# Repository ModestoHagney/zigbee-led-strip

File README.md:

| Supported Targets | ESP32-C6 | ESP32-H2 |
| ----------------- | -------- | -------- |

# Zigbee LED Strip

Firmware that turns an ESP32-H2 or ESP32-C6 and a WS2812 strip into a
Zigbee colour light. It joins the network as a router (it relays for
other Zigbee devices, like a mains-powered bulb) and shows up in Home
Assistant as one colour dimmable light (on/off, brightness, and colour
in either hue/saturation or XY).

The whole strip is one light: every pixel gets the same colour.

## Boards

One source builds for both chips. `main/config.h` picks the settings
from the chip target:

| Target   | LED data pin | LED count | Zigbee model |
|----------|--------------|-----------|--------------|
| ESP32-H2 | GPIO 22      | 64        | `H2-LED`     |
| ESP32-C6 | GPIO 19      | 144       | `C6-LED`     |

The LED count in the table is only the default, see Settings below.
Manufacturer name is `NiftyFish`. Power source and the Zigbee endpoint
are set in `main/config.h`.

## Settings in Home Assistant

These are changed on the device page in Home Assistant (ZHA) and saved
on the board. `main/config.h` holds the defaults a freshly flashed board
starts with.

| Setting | Range | Notes |
|---------|-------|-------|
| LED count | 1 to 1024 | |
| Colour order | GRB, RGB, BRG, RBG, GBR, BGR | for strips that show the wrong colours |
| LED type | RGB, RGBW | RGBW sends white to the strip's white LED |
| Max current | 0 to 65000 mA | dims the strip to stay under it, 0 = no limit |
| White balance red, green, blue | 0 to 100 % | so white matches other bulbs |
| Dimming curve | 10 to 30 | 10 = straight, 22 = like most bulbs |
| Zigbee transmit power | -24 to 20 dBm | |
| Start-up behaviour | off, on, toggle, previous | what the strip does when power returns |
| On/off transition time | tenths of a second | fade when switching, 0 = no fade |

The last two are standard Zigbee settings that ZHA shows by itself. The
rest need the quirk file: copy `homeassistant/niftyfish_led.py` to
`/config/zha_quirks/` in Home Assistant, add this to
`configuration.yaml` and restart:

```yaml
zha:
  custom_quirks_path: /config/zha_quirks/
```

The device also reports the chip temperature and an estimated strip
power. The estimate is worked out from colour, brightness and LED count
with `LED_MA_PER_CHANNEL` and `LED_VOLTS` from `main/config.h`; the
current limit uses the same numbers.

The Identify button blinks the strip white.

The last colour, brightness and on/off state are saved a few seconds
after they change and come back after a power cut.

## Hardware

`hardware/ZigbeeLEDController/` is the KiCad 9 project for the
controller board: an ESP32-C6-MINI-1 with a USB-C input, a CH221K USB
PD sink, an AP63203 3.3 V buck regulator and an LED strip output. The
folder also has the PCBWay fabrication zip (`.kicad_pcb.zip`: gerbers,
BOM and positions) and a STEP export of the board.

## Build and flash

Needs ESP-IDF 5.x (built with v5.5.2).

```
idf.py set-target esp32h2
idf.py -p PORT flash monitor
```

Use `esp32c6` for the C6 board. Switching target regenerates
`sdkconfig` and `dependencies.lock`; neither is committed.

Run `idf.py -p PORT erase-flash` first if the board has been paired
before and you want it to join as a new device. This is also needed
once for a board flashed before wireless updates were added, because
the partition layout changed; then remove it from ZHA and pair it again.

An existing `sdkconfig` keeps the old end-device setting. Delete it (or
run `idf.py set-target` again) so `sdkconfig.defaults` applies.

The partition table has two firmware slots of 896 KB each and fits 2 MB
flash.

## Wireless updates

After the first USB flash, new firmware can be sent over Zigbee from
Home Assistant. Home Assistant downloads it from the `firmware` branch
of this repo, so the repo has to be public.

One-time setup in Home Assistant: add this to `configuration.yaml` and
restart.

```yaml
zha:
  zigpy_config:
    ota:
      extra_providers:
        - type: z2m
          url: https://raw.githubusercontent.com/ModestoHagney/zigbee-led-strip/firmware/index.json
```

Home Assistant checks that index once a day (and when it restarts). A
board asks Home Assistant for updates when it joins and then every
hour; when a newer version is listed, its Firmware entity offers it.

To publish an update:

1. Raise `FW_VERSION` in `main/config.h`.
2. `idf.py build`, once per chip.
3. `python tools/make_ota.py` writes `build/niftyfish-<chip>-led-v<version>.ota`.
4. On the `firmware` branch, replace the old `.ota` file with the new
   one, then run
   `python tools/make_index.py . https://raw.githubusercontent.com/ModestoHagney/zigbee-led-strip/firmware`
   and commit and push.

The `firmware` branch also carries the 4-button light's update file, so
one line in Home Assistant covers every NiftyFish device.

An H2 file is never offered to a C6 board, or a strip file to the
4-button light: each has its own image type. If new firmware crashes
before it starts Zigbee, the board goes back to the previous one on the
next boot.

Without GitHub: put the `.ota` file in a folder on the Home Assistant
machine and list that folder as a `type: advanced` provider instead
(ZHA's documentation has the exact lines).

## Pairing

On first boot (or after an erase) the device starts network steering
on its own. Put the coordinator into permit-join and it should log
`joined network! ready.`

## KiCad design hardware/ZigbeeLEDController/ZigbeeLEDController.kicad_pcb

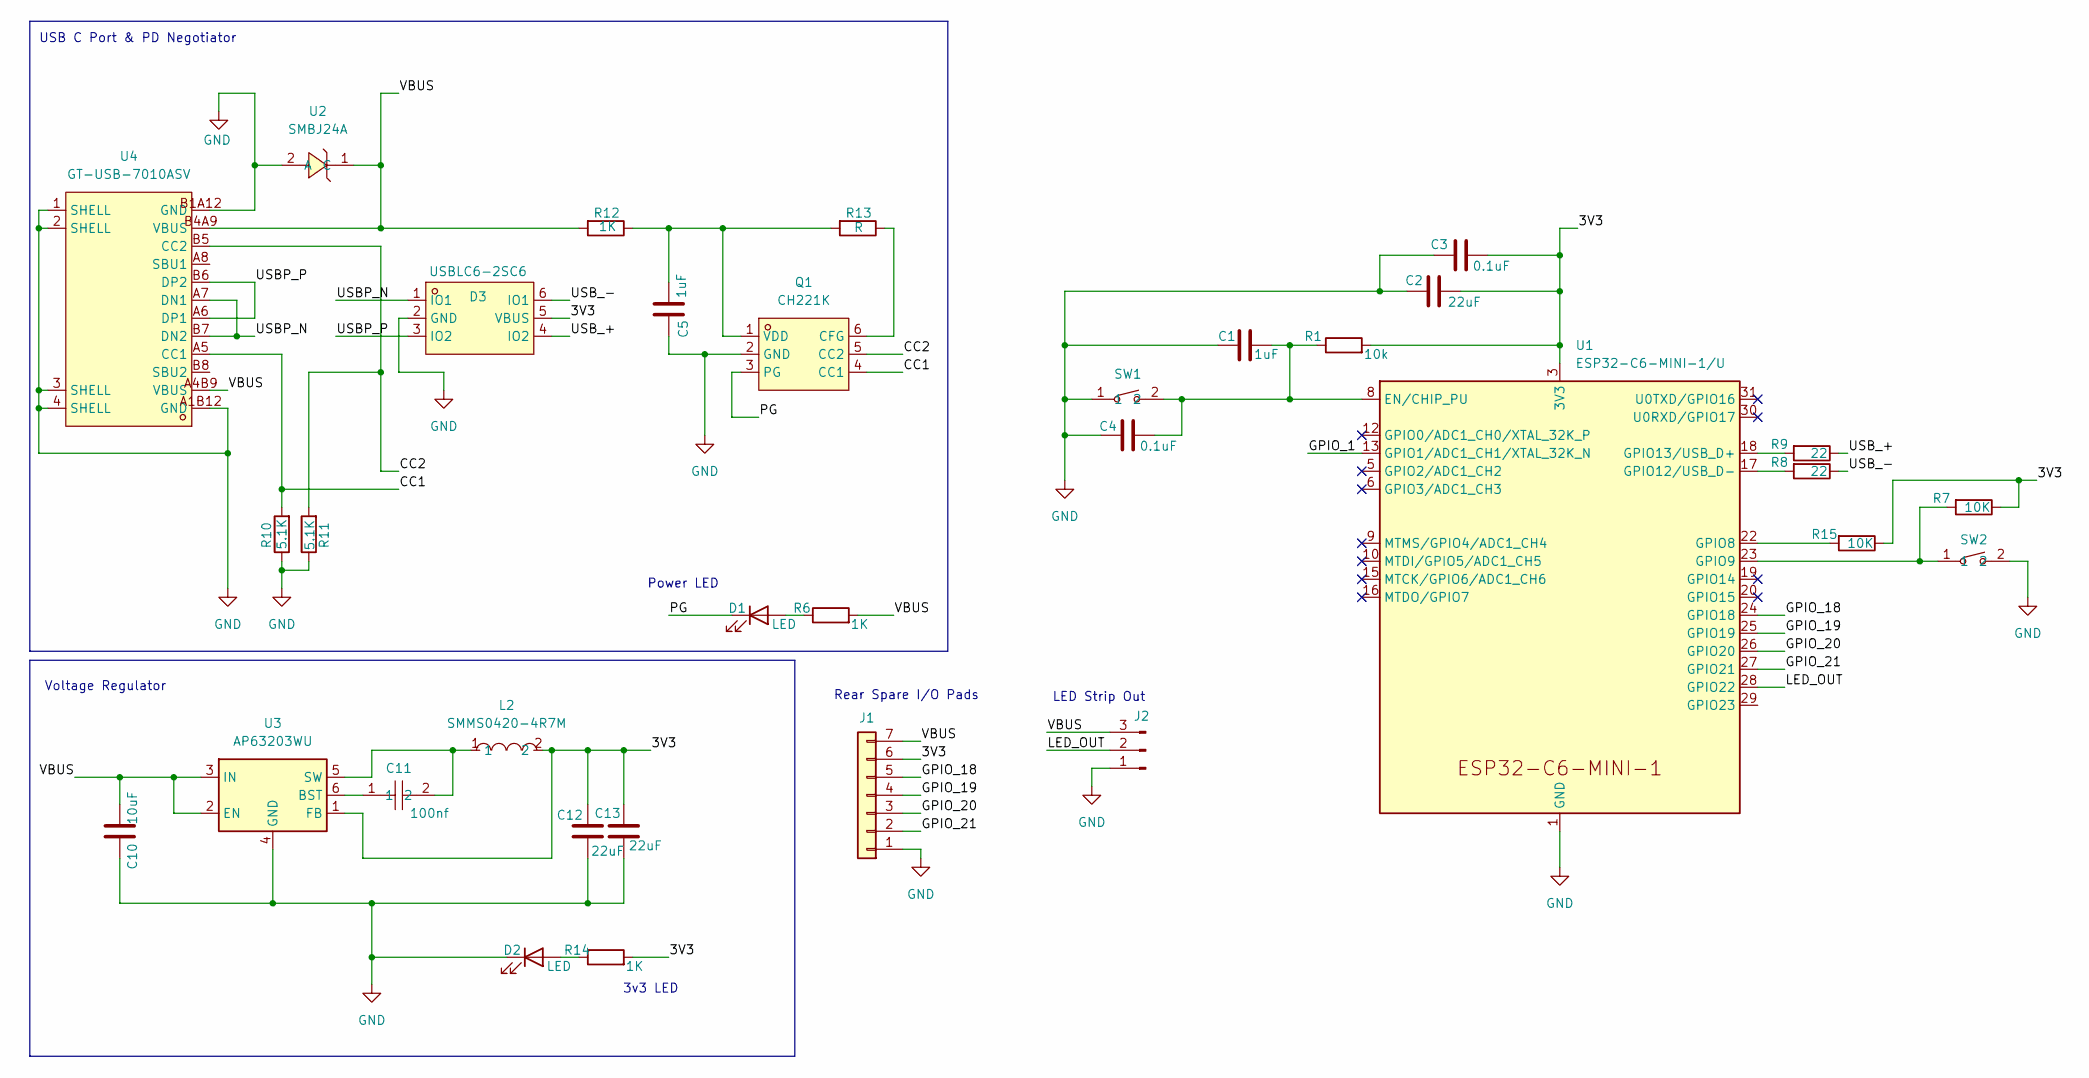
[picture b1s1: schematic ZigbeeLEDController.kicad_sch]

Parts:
C1, C5: 1uF; C_0805_2012Metric
C2, C12, C13: 22uF; C_0805_2012Metric
C3, C4: 0.1uF; C_0805_2012Metric
C10: 10uF; C_0805_2012Metric
C11: 100nf; C_0805_2012Metric; MPN CC0805KRX7R9BB104; LCSC Part C49678
D1, D2: LED; LED_0805_2012Metric
D3: USBLC6-2SC6; SOT-23-6_L2.9-W1.6-P0.95-LS2.8-BL; MPN USBLC6-2SC6; LCSC Part C2827654
J1: Conn_01x07; 1x07_SOLDER_PAD_1.7x4_LABEL
J2: Conn_01x03_Pin; PinSocket_1x03_P2.54mm_Vertical
L2: SMMS0420-4R7M; IND-SMD_L4.8-W4.5; MPN SMMS0420-4R7M; LCSC Part C133193
Q1: CH221K; SOT-23-6_L2.9-W1.6-P0.95-LS2.8-BL-2; MPN CH221K; LCSC Part C5125736
R1: 10k; R_0805_2012Metric
R6, R12, R14: 1K; R_0805_2012Metric
R7, R15: 10K; R_0805_2012Metric
R8, R9: 22; R_0805_2012Metric
R10, R11: 5.1K; R_0805_2012Metric
R13: R; R_0805_2012Metric
SW1, SW2: HX-B3U-1000P-1.6N; SW-SMD_2P-L3.0-W2.5-LS4.0; MPN HX-B3U-1000P-1.6N; LCSC Part C49234121
U1: ESP32-C6-MINI-1/U; ESP32-C6-MINI-1
U2: SMBJ24A; SMB_L4.3-W3.6-LS5.3-RD; MPN SMBJ24A; LCSC Part C19077578
U3: AP63203WU; TSOT-23-6
U4: GT-USB-7010ASV; USB-C-SMD_G-SWITCH_GT-USB-7010ASV; MPN GT-USB-7010ASV; LCSC Part C2988369

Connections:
/3V3: C2.2, C3.2, C12.1, C13.1, D3.5 (VBUS), J1.6, L2.2, R1.2, R7.1, R14.2, R15.1, U1.3 (3V3), U3.1 (FB)
/CC1: Q1.4 (CC1), R10.2, U4.A5 (CC1)
/CC2: Q1.5 (CC2), R11.2, U4.B5 (CC2)
/GPIO_1: U1.13 (GPIO1/ADC1_CH1/XTAL_32K_N)
/GPIO_18: J1.5, U1.24 (GPIO18)
/GPIO_19: J1.4, U1.25 (GPIO19)
/GPIO_20: J1.3, U1.26 (GPIO20)
/GPIO_21: J1.2, U1.27 (GPIO21)
/LED_OUT: J2.2, U1.28 (GPIO22)
/PG: D1.1 (K), Q1.3 (PG)
/USBP_N: D3.1 (IO1), U4.A7 (DN1), U4.B7 (DN2)
/USBP_P: D3.3 (IO2), U4.A6 (DP1), U4.B6 (DP2)
/USB_+: D3.4 (IO2), R9.1
/USB_-: D3.6 (IO1), R8.1
/VBUS: C10.1, J1.7, J2.3, R6.2, R12.2, U2.1 (C), U3.2 (EN), U3.3 (IN), U4.A4B9 (VBUS), U4.B4A9 (VBUS)
GND: C1.1, C2.1, C3.1, C4.2, C5.2, C10.2, C12.2, C13.2, D2.1 (K), D3.2 (GND), J1.1, J2.1, Q1.2 (GND), R10.1, R11.1, SW1.1, SW2.2, U1.1 (GND), U1.2 (GND), U1.11 (GND), U1.14 (GND), U1.36 (GND), U1.37 (GND), U1.38 (GND), U1.39 (GND), U1.40 (GND), U1.41 (GND), U1.42 (GND), U1.43 (GND), U1.44 (GND), U1.45 (GND), U1.46 (GND), U1.47 (GND), U1.48 (GND), U1.49 (GND), U1.50 (GND), U1.51 (GND), U1.52 (GND), U1.53 (GND), U2.2 (A), U3.4 (GND), U4.1 (SHELL), U4.2 (SHELL), U4.3 (SHELL), U4.4 (SHELL), U4.A1B12 (GND), U4.B1A12 (GND)
unnamed: D1.2 (A), R6.1
unnamed: D2.2 (A), R14.1
unnamed: Q1.6 (CFG), R13.1
unnamed: C5.1, Q1.1 (VDD), R12.1, R13.2
unnamed: C1.2, C4.1, R1.1, SW1.2, U1.8 (EN/CHIP_PU)
unnamed: R15.2, U1.22 (GPIO8)
unnamed: R7.2, SW2.1, U1.23 (GPIO9)
unnamed: R8.2, U1.17 (GPIO12/USB_D-)
unnamed: R9.2, U1.18 (GPIO13/USB_D+)
unnamed: C11.1, U3.6 (BST)
unnamed: C11.2, L2.1, U3.5 (SW)

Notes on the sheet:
LED Strip Out
Power LED
3v3 LED
USB C Port & PD Negotiator
Voltage Regulator
Rear Spare I/O Pads

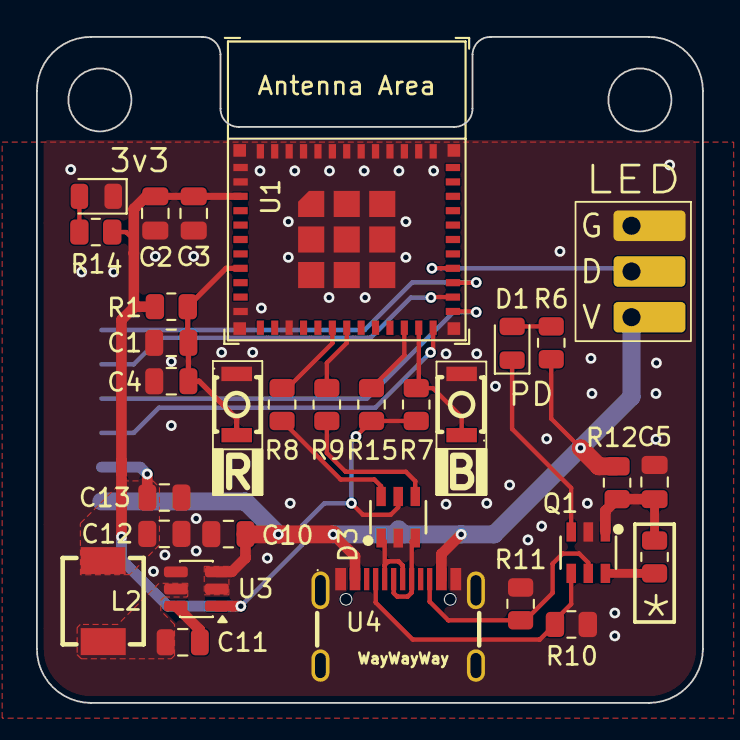
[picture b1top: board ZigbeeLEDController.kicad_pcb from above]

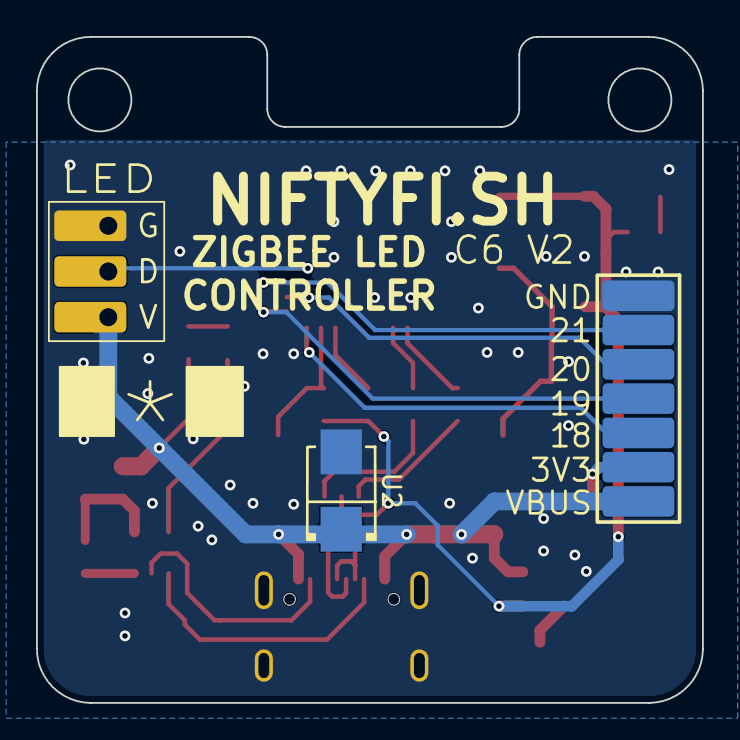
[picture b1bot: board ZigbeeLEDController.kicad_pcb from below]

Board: 2 copper layers, 37.0 x 37.0 mm, 33 parts (3 on the bottom side), 26 nets.
